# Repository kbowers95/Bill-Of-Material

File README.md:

Catch the Light Game
Description: A new speed and reflex game. Quickly press the lit buttons in a certain amount of time.

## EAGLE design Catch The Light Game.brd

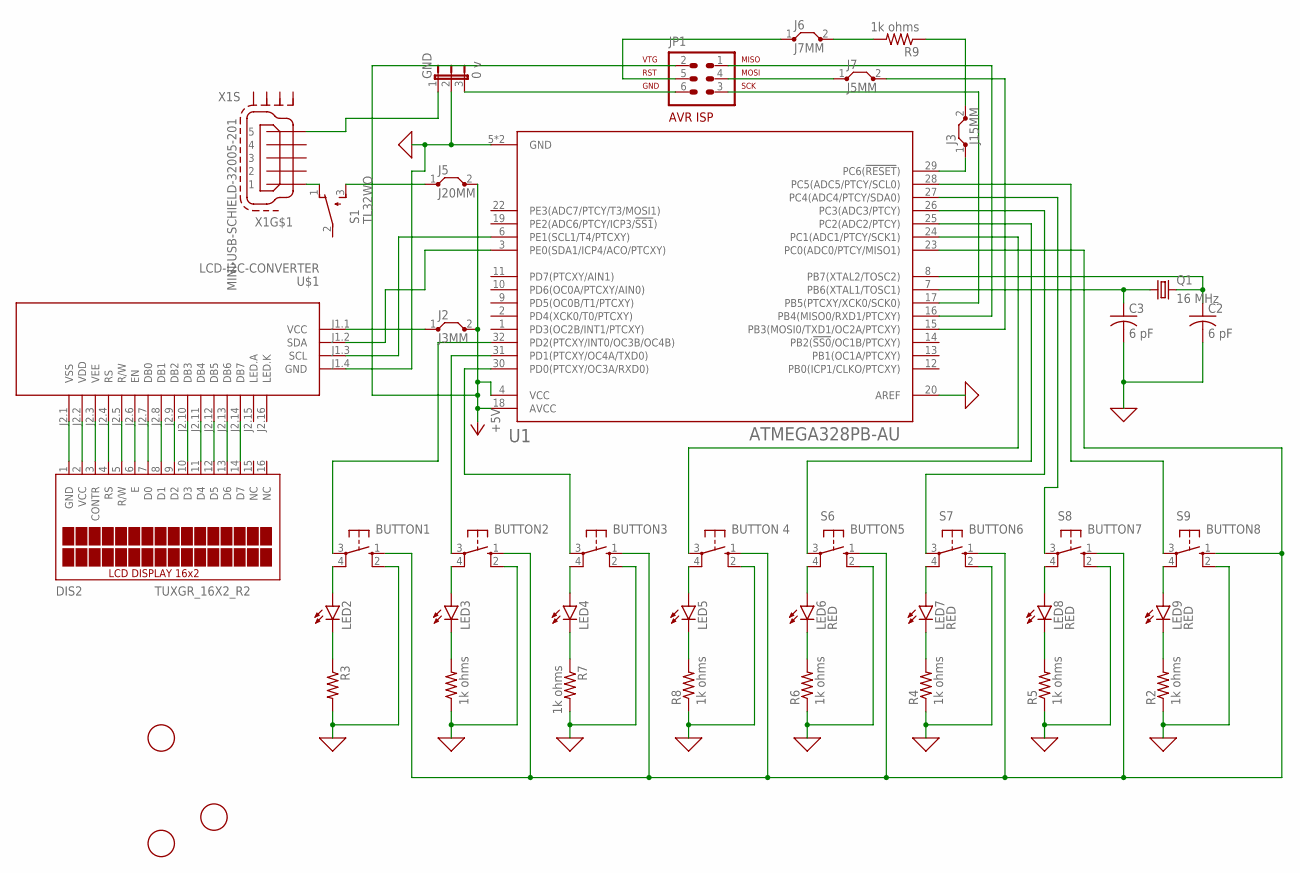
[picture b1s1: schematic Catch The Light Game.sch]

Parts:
C2, C3: 6 pF; C025-024X044
DIS2: TUXGR_16X2_R2
GND: 0 v; JP2
J2: J3MM; 03
J3: J15MM; 15
J5: J20MM; 20
J6: J7MM; 07
J7: J5MM; 05
JP1: AVR-ISP-6R
LED2, LED3, LED4, LED5, LED6, LED7, LED8, LED9: RED; LED5MM
Q1: 16 MHz; HC49/S
R1, R2, R4, R5, R6, R7, R8, R9: 1k ohms; 0204/5
R3: 1K ohms; 0204/5
S1: TL32WO; TL3XWO
S2: BUTTON1; B3F-10XX
S3: BUTTON2; B3F-10XX
S4: BUTTON3; B3F-10XX
S5: BUTTON 4; B3F-10XX
S6: BUTTON5; B3F-10XX
S7: BUTTON6; B3F-10XX
S8: BUTTON7; B3F-10XX
S9: BUTTON8; B3F-10XX
U1: ATMEGA328PB-AU; QFP80P900X900X120-32N
U$1: LCD-I2C-CONVERTER
U$2, U$3, U$4: FIDUCIAL; FIDUCIAL_1MM
X1: MINI-USB-SCHIELD-32005-201; 32005-201

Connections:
0: C2.2, C3.2, GND.2, R1.1, R2.1, R3.2, R4.1, R5.1, R6.1, R7.2, R8.1, S2.2 (S1), S3.2 (S1), S4.2 (S1), S5.2 (S1), S6.2 (S1), S7.2 (S1), S8.2 (S1), S9.2 (S1), U1.5 (GND), U1.20 (AREF), U1.21 (GND), U$1.J1.4 (GND); also elsewhere on the board
unnamed: DIS2.7 (D0), U$1.J2.7 (DB0)
unnamed: DIS2.8 (D1), U$1.J2.8 (DB1)
unnamed: DIS2.9 (D2), U$1.J2.9 (DB2)
unnamed: DIS2.10 (D3), U$1.J2.10 (DB3)
unnamed: DIS2.11 (D4), U$1.J2.11 (DB4)
unnamed: DIS2.12 (D5), U$1.J2.12 (DB5)
unnamed: DIS2.13 (D6), U$1.J2.13 (DB6)
unnamed: JP1.3, U1.17 (PB5(PTCXY/XCK0/SCK0))
unnamed: LED3.K (C), R1.2
unnamed: LED3.A, S3.4 (P1)
unnamed: S8.3, U1.27 (PC4(ADC4/PTCY/SDA0))
unnamed: S4.3, U1.30 (PD0(PTCXY/OC3A/RXD0))
unnamed: LED4.A, S4.4 (P1)
unnamed: J7.2, U1.15 (PB3(MOSI0/TXD1/OC2A/PTCXY))
unnamed: LED8.A, S8.4 (P1)
unnamed: LED7.K (C), R4.2
unnamed: LED9.A, S9.4 (P1)
unnamed: LED6.A, S6.4 (P1)
unnamed: S5.3, U1.24 (PC1(ADC1/PTCY/SCK1))
unnamed: S6.3, U1.25 (PC2(ADC2/PTCY))
unnamed: S7.3, U1.26 (PC3(ADC3/PTCY))
unnamed: DIS2.14 (D7), U$1.J2.14 (DB7)
unnamed: DIS2.4 (RS), U$1.J2.4 (RS)
unnamed: GND.1, X1.5
unnamed: DIS2.5 (R/W), U$1.J2.5 (R/W)
unnamed: DIS2.6 (E), U$1.J2.6 (EN)
unnamed: S9.3, U1.28 (PC5(ADC5/PTCY/SCL0))
unnamed: S3.3, U1.31 (PD1(PTCXY/OC4A/TXD0))
unnamed: JP1.1, U1.16 (PB4(MISO0/RXD1/PTCXY))
unnamed: J2.1, U$1.J1.1 (VCC)
unnamed: DIS2.1 (GND), U$1.J2.1 (VSS)
unnamed: DIS2.2 (VCC), U$1.J2.2 (VDD)
unnamed: DIS2.3 (CONTR), U$1.J2.3 (VEE)
unnamed: U1.3 (PE0(SDA1/ICP4/ACO/PTCXY)), U$1.J1.2 (SDA)
unnamed: S2.1 (S), S3.1 (S), S4.1 (S), S5.1 (S), S6.1 (S), S7.1 (S), S8.1 (S), S9.1 (S), U1.23 (PC0(ADC0/PTCY/MISO1))
unnamed: LED5.A, S5.4 (P1)
unnamed: LED4.K (C), R7.1
unnamed: S1.1 (O), X1.1
unnamed: J6.1, JP1.5
unnamed: U1.6 (PE1(SCL1/T4/PTCXY)), U$1.J1.3 (SCL)
unnamed: J6.2, R9.2
unnamed: C2.1, Q1.2, U1.8 (PB7(XTAL2/TOSC2))
unnamed: C3.1, Q1.1, U1.7 (PB6(XTAL1/TOSC1))
unnamed: J3.1, U1.29 (PC6(!RESET!))
unnamed: GND.3, JP1.6
unnamed: J7.1, JP1.4
unnamed: LED5.K (C), R8.2
unnamed: J5.1, S1.3 (S)
unnamed: LED2.K (C), R3.1
unnamed: J3.2, R9.1
unnamed: S2.3, U1.32 (PD2(PTCXY/INT0/OC3B/OC4B))
unnamed: LED6.K (C), R6.2
unnamed: LED7.A, S7.4 (P1)
unnamed: LED8.K (C), R5.2
unnamed: LED9.K (C), R2.2
unnamed: LED2.A, S2.4 (P1)
VCC: J2.2, J5.2, JP1.2, U1.4 (VCC), U1.18 (AVCC); also elsewhere on the board

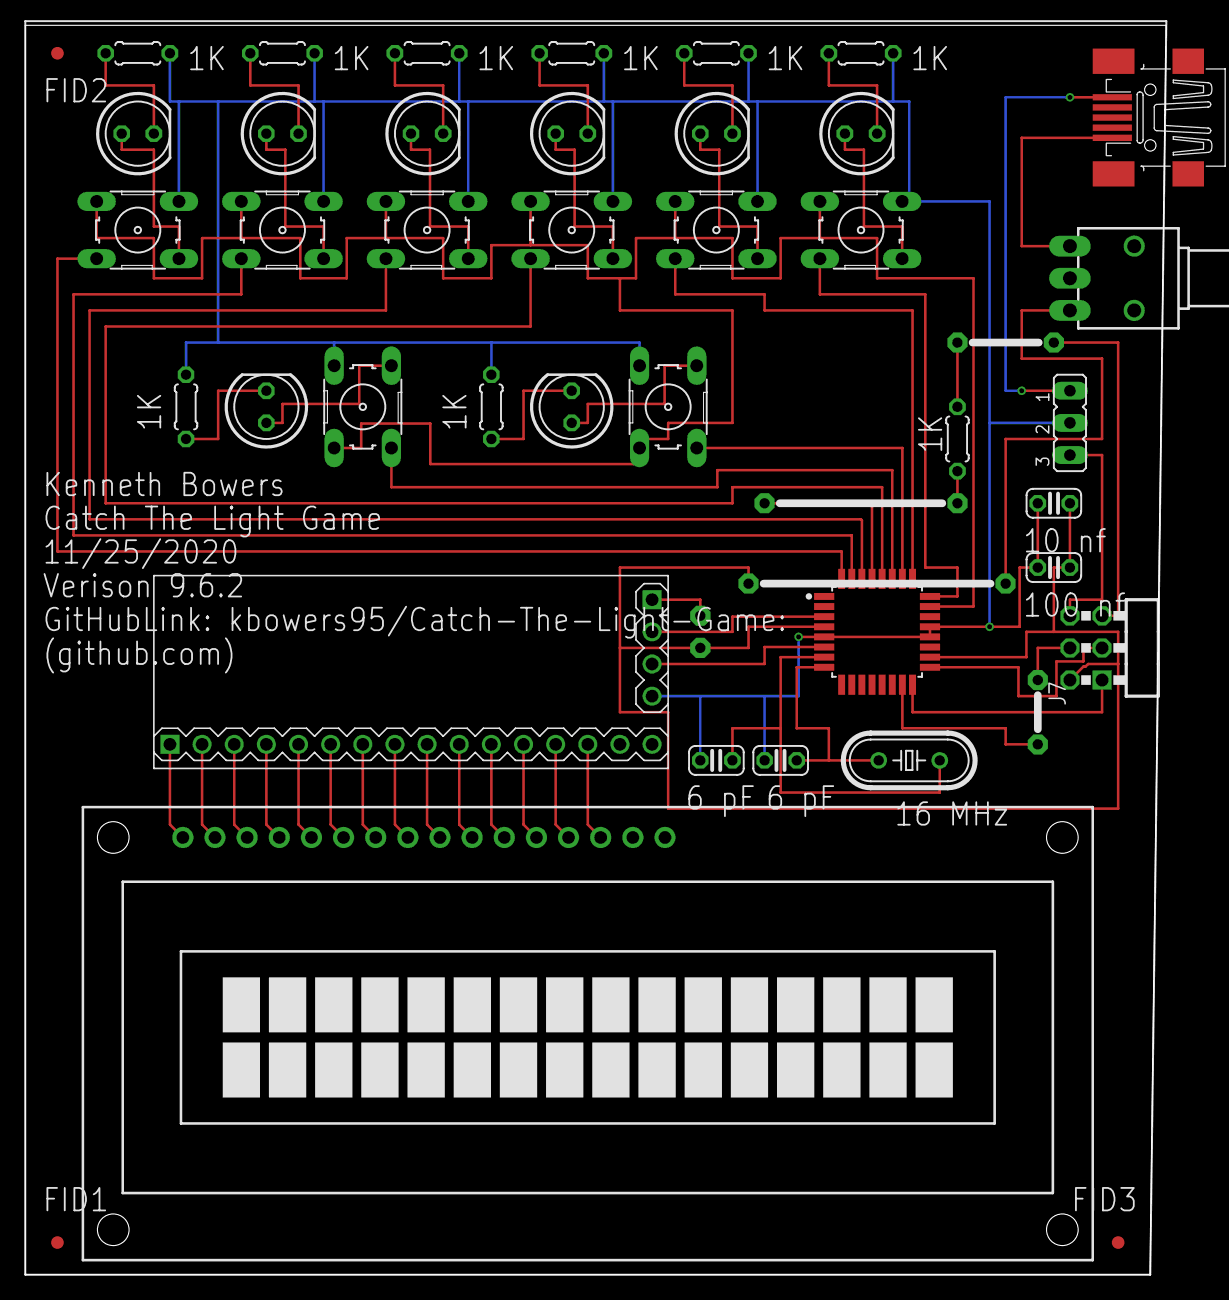
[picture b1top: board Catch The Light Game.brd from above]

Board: 2 copper layers, 90.2 x 98.7 mm, 45 parts (0 on the bottom side), 58 nets.

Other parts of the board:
C1: 100 nf; C025-024X044
C4: 10 nf; C025-024X044

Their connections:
0: C1.1, C4.1; also elsewhere on the board
VCC: C1.2, C4.2; also elsewhere on the board

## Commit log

2020-10-20 Rename FinalPRoject.csv to BOM
2020-11-07 Create Schematic Submission
2020-11-07 Rename Board Submission.brd to Gerber Submission.brd
2020-11-12 Create CAM OUTPUT
2020-11-12 Create k
2020-11-12 Create Veritfication
2020-11-12 Update Veritfication
2020-11-12 Create Assembly
2020-11-12 Create g
2020-11-12 Create a
2020-11-12 Create b
2020-11-24 Create gitignore
2020-11-25 Create as
2020-11-25 Rename solderpaste_bottom.gbr to CatchTheLight.GBS
2020-11-25 Rename soldermask_top.gbr to CatchTheLight.GTS
2020-11-25 Rename solderpaste_top.gbr to CatchTheLight.GTP
2020-11-25 Rename silkscreen_top.gbr to CatchTheLight.GTO
2020-11-25 Rename copper_top.gbr to CatchTheLight.GTL
2020-11-25 Rename profile.gbr to CatchTheLight.GKO
2020-11-25 Rename CatchTheLight.GBS to CatchTheLight.GBP
2020-11-25 Rename soldermask_bottom.gbr to CatchTheLight.GBS
2020-11-25 Rename copper_bottom.gbr to CatchTheLight.GBL
2020-11-25 Rename silkscreen_bottom.gbr to CatchTheLight.GBO
2020-12-09 Create Demo video explanation

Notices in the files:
parts and their libraries:
diy-modules: Released under the Creative Commons Attribution 4.0 International License: http://creativecommons.org/licenses/by/4.0
